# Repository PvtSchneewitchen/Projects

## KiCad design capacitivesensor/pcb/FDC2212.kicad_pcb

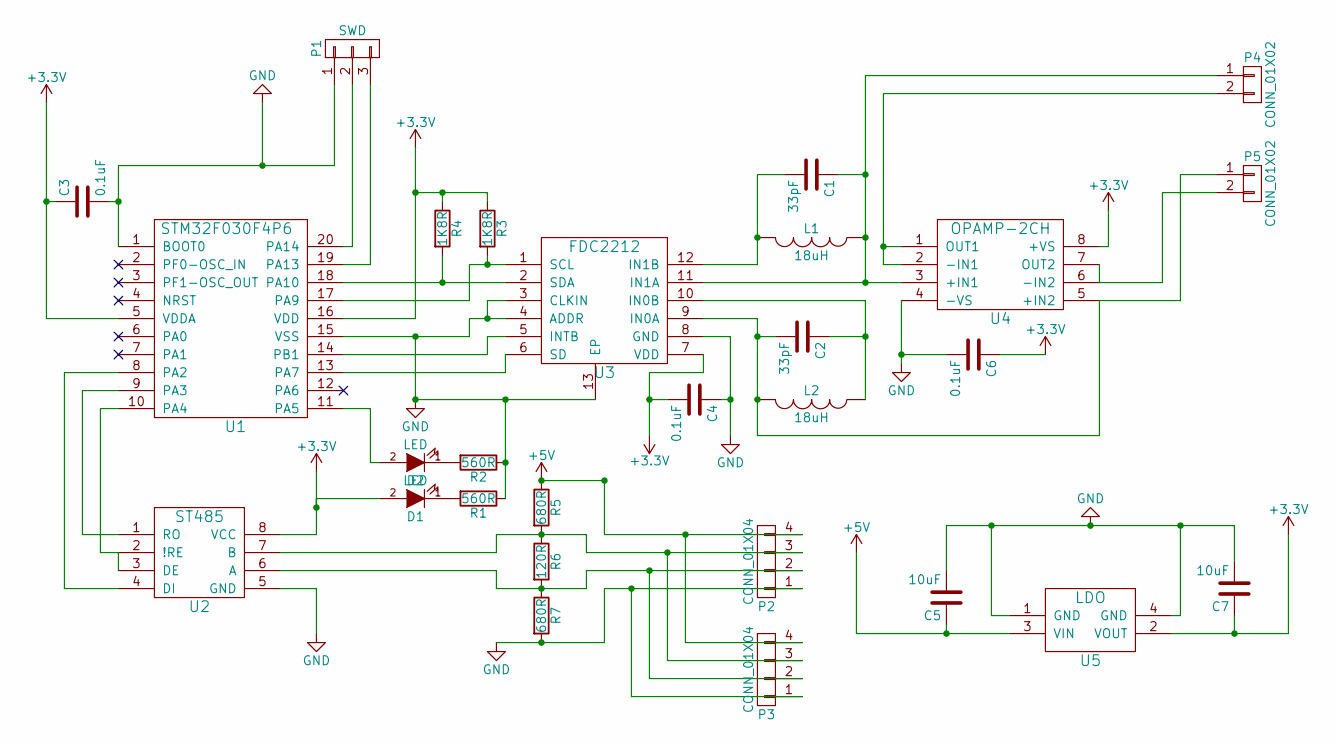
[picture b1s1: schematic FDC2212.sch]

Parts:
C1, C2: 33pF; C_0603_HandSoldering
C3, C4, C6: 0.1uF; C_0603_HandSoldering
C5, C7: 10uF; C_0603_HandSoldering
D1, D2: LED; LED_0603
L1, L2: 18uH; R_1210_HandSoldering
P1: SWD; Pin_Header_Straight_1x03
P2, P3: CONN_01X04; Pin_Header_Straight_1x04
P4, P5: CONN_01X02; SMB_Straight
R1, R2: 560R; R_0603_HandSoldering
R3, R4: 1K8R; R_0603_HandSoldering
R5, R7: 680R; R_0603_HandSoldering
R6: 120R; R_0603_HandSoldering
U1: STM32F030F4P6; TSSOP-20_4.4x6.5mm_Pitch0.65mm
U2: ST485; SOIC-8_3.9x4.9mm_Pitch1.27mm
U3: FDC2212; DFN-12-1EP_4x4mm_Pitch0.5mm
U4: OPAMP-2CH; MSOP-8_3x3mm_Pitch0.65mm
U5: LDO; SOT-223

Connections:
+3V3: C3.1, C4.2, C6.1, C7.1, D1.2 (A), R3.1, R4.1, U1.5 (VDDA), U1.16 (VDD), U2.8 (VCC), U3.7 (VDD), U4.8 (+VS), U5.2 (VOUT)
+5V: C5.1, P2.4, P3.4, R5.1, U5.3 (VIN)
GND: C3.2, C4.1, C5.2, C6.2, C7.2, P1.1, P2.1, P3.1, R1.1, R2.1, R7.2, U1.1 (BOOT0), U1.15 (VSS), U2.5 (GND), U3.3 (CLKIN), U3.4 (ADDR), U3.8 (GND), U3.13 (EP), U4.4 (-VS), U5.1 (GND), U5.4 (GND)
unnamed: C1.1, L1.1, P4.1, U3.11 (IN1A), U4.3 (+IN1)
unnamed: C1.2, L1.2, U3.12 (IN1B)
unnamed: C2.1, L2.1, U3.10 (IN0B)
unnamed: C2.2, L2.2, P5.1, U3.9 (IN0A), U4.5 (+IN2)
unnamed: D1.1 (K), R1.2
unnamed: D2.1 (K), R2.2
unnamed: D2.2 (A), U1.11 (PA5)
unnamed: P1.2, U1.20 (PA14)
unnamed: P1.3, U1.19 (PA13)
unnamed: P2.2, P3.2, R6.2, R7.1, U2.6 (A)
unnamed: P2.3, P3.3, R5.2, R6.1, U2.7 (B)
unnamed: P4.2, U4.1 (OUT1), U4.2 (-IN1)
unnamed: P5.2, U4.6 (-IN2), U4.7 (OUT2)
unnamed: R3.2, U1.17 (PA9), U3.1 (SCL)
unnamed: R4.2, U1.18 (PA10), U3.2 (SDA)
unnamed: U1.8 (PA2), U2.4 (DI)
unnamed: U1.9 (PA3), U2.1 (RO)
unnamed: U1.10 (PA4), U2.2 (!RE), U2.3 (DE)
unnamed: U1.13 (PA7), U3.6 (SD)
unnamed: U1.14 (PB1), U3.5 (INTB)

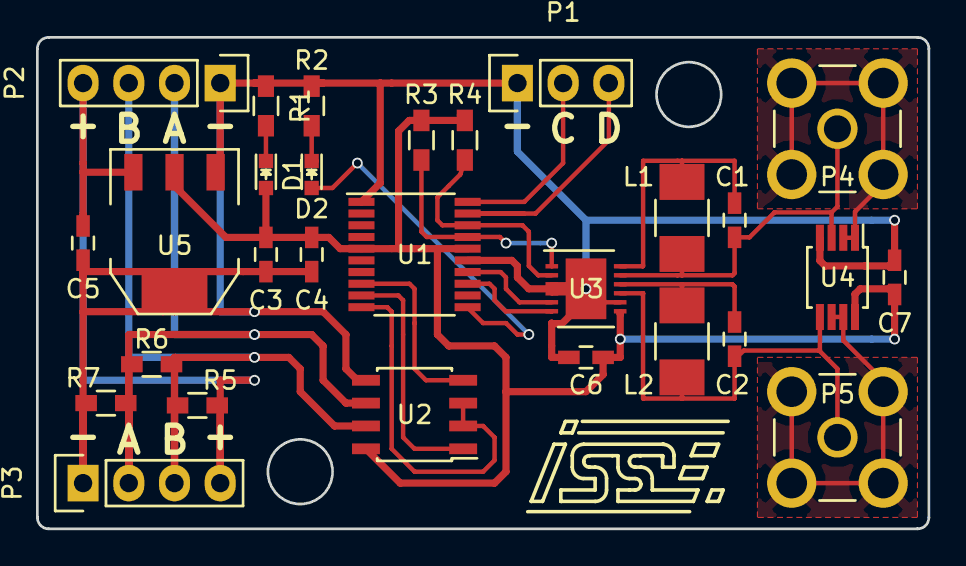
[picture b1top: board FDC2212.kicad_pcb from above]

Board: 2 copper layers, 49.5 x 27.3 mm, 28 parts (0 on the bottom side), 23 nets.

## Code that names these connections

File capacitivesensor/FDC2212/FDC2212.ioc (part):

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Mcu.Name=STM32F030F4Px
Mcu.Package=TSSOP20
Mcu.UserName=STM32F030F4Px
PA10.GPIOParameters=GPIO_Label
PA10.GPIO_Label=I2C_SDA
PA10.Mode=I2C
PA10.Signal=I2C1_SDA
PA13.GPIOParameters=GPIO_Label
PA13.GPIO_Label=SWD_IO
PA13.Mode=Serial-WireDebug
PA13.Signal=SYS_SWDIO
PA14.GPIOParameters=GPIO_Label
PA14.GPIO_Label=SWT_CL
PA14.Mode=Serial-WireDebug
PA14.Signal=SYS_SWCLK
PA2.GPIOParameters=GPIO_Label
PA2.GPIO_Label=UART_TX
PA2.Mode=Asynchronous
PA2.Signal=USART1_TX
PA3.GPIOParameters=GPIO_Label
PA3.GPIO_Label=UART_RX
PA3.Mode=Asynchronous
PA3.Signal=USART1_RX
PA4.GPIOParameters=GPIO_Speed,GPIO_Label
PA4.GPIO_Label=UART_DE
PA4.GPIO_Speed=GPIO_SPEED_HIGH
PA4.Signal=GPIO_Output
PA5.GPIOParameters=GPIO_Label
PA5.GPIO_Label=LED
PA5.Signal=GPIO_Output
PA7.GPIOParameters=GPIO_Label
PA7.GPIO_Label=I2C_SD
PA7.Signal=GPIO_Output
PA9.GPIOParameters=GPIO_Label
PA9.GPIO_Label=I2C_SCL
PA9.Mode=I2C
PA9.Signal=I2C1_SCL
PB1.GPIOParameters=GPIO_Label
PB1.GPIO_Label=I2C_INT
PB1.Signal=GPIO_Input
RCC.SYSCLKFreq_VALUE=48000000
RCC.SYSCLKSource=RCC_SYSCLKSOURCE_PLLCLK
board=FDC2212

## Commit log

2017-11-06 holo
2017-11-06 sender
2017-11-06 connection
2017-11-07 connection build
2017-11-07 add sensor
2017-11-07 add vicontest
2017-11-08 Vicon access to sensorviewer
2017-11-08 viconaccess.java
2017-11-09 better viconaccess and logging
2017-11-09 holoconection project import
2017-11-09 probably finished connection
2017-11-10 holoconection
2017-11-10 holo conection holo
2017-11-11 improve hololensconnection
2017-11-11 holoconnect impr
2017-11-11 spatial boundaries sind schon wieder kaputt
2017-11-11 holo connection integration in sensorview
2017-11-23 electrical field tryout
2017-11-30 push
2017-12-05 print logged positions of sphere
2017-12-08 Final Field implementation, code comment, und auslagerung
2018-01-10 multicast
2018-01-10 listen
2018-01-10 relb
2018-01-10 fwef
2018-01-10 wfeg
2018-01-10 sfdsa
2018-01-10 fewf
2018-01-11 vfewev
2018-01-11 fwgw
2018-01-16 djdjd
